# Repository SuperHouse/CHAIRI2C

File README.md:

Chair I2C Interface
===================
Copyright 2020 SuperHouse Automation Pty Ltd <www.superhouse.tv>  
Designed by Jonathan Oxer

Connects to a Permobil electric wheelchair controller, and emulates the
signls from a wheelchair joystick so that the chair can be controlled
electronically. Provides an I2C interface for connection to a host
microcontroller.

Also exposes the "5th Button" and 12V 100mA chair power connections.

Features:

 * 1 x chair controller output.
 * I2C interface.
 * Derives 12V power from the host wheelchair controller.
 * Requires 2.7-5.5V external logic power.

More information is available at:

  http://www.superhouse.tv/chairi2c

INSTALLATION
------------
The design is saved as an EAGLE project. EAGLE PCB design software is
available from www.cadsoftusa.com free for non-commercial use. To use
this project download it and place the directory containing these files
into the "eagle" directory on your computer. Then open EAGLE and
navigate to the project.

DISTRIBUTION
------------
The specific terms of distribution of this project are governed by the
license referenced below.

LICENSE
-------
Licensed under the TAPR Open Hardware License (www.tapr.org/OHL).
The "license" folder within this repository also contains a copy of
this license in plain text format.

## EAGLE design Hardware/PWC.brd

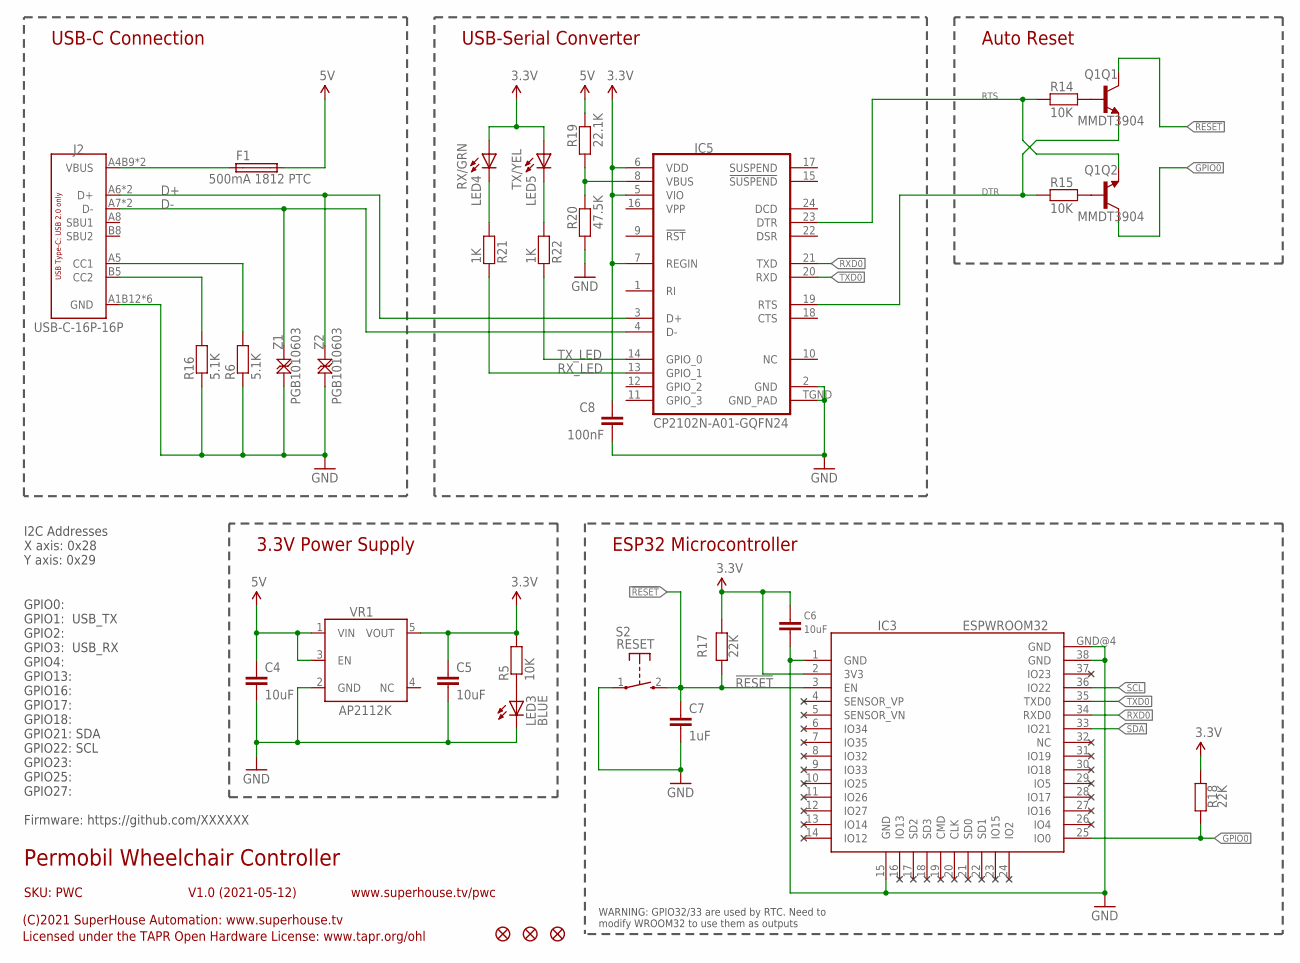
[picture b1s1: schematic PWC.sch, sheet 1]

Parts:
C4, C5, C6: 10uF; C0805
C7: 1uF; C0603
C8: 100nF; C0603
F1: 500mA 1812 PTC; 1812
IC3: ESPWROOM32
IC5: CP2102N-A01-GQFN24; QFN-24
J2: USB-C-16P-16P; USB-C-16P
LED3: BLUE; LED-0603
LED4: RX/GRN; LED-0603
LED5: TX/YEL; LED-0603
Q1: MMDT3904; SOT-363
R5, R14, R15: 10K; R0603
R6, R16: 5.1K; R0603
R17, R18: 22K; R0603
R19: 22.1K; R0603
R20: 47.5K; R0603
R21, R22: 1K; R0603
S2: RESET; TACTILE_SMT_3X4X2
U$35, U$36, U$37: FIDUCIAL1X2; FIDUCIAL-1X2
VR1: AP2112KSOT25; SOT23-5
Z1, Z2: PGB1010603; TVS0603

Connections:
3.3V: C5.1, C6.1, C8.1, IC3.2 (3V3), IC5.5 (VIO), IC5.6 (VDD), IC5.7 (REGIN), LED4.A, LED5.A, R5.2, R17.1, R18.1, VR1.5 (VOUT); also elsewhere on the board
5V: C4.1, F1.2, R19.2, VR1.1 (VIN), VR1.3 (EN)
!RESET: C7.1, IC3.3 (EN), Q1.3 (C), R17.2, S2.2 (S)
D+: IC5.3 (D+), J2.A6 (D+), J2.B6 (D+), Z2.2
D-: IC5.4 (D-), J2.A7 (D-), J2.B7 (D-), Z1.2
DTR: IC5.23 (DTR), Q1.1 (E), R14.1
GND: C4.2, C5.2, C6.2, C7.2, C8.2, IC3.1 (GND), IC3.15 (GND), IC3.38 (GND), IC3.GND@4 (GND), IC5.2 (GND), IC5.TGND (GND_PAD), J2.A1B12 (GND), J2.A12B1 (GND), J2.FIX1 (GND), J2.FIX2 (GND), J2.FIX3 (GND), J2.FIX4 (GND), LED3.C, R6.1, R16.1, R20.1, S2.1, VR1.2 (GND), Z1.1, Z2.1; also elsewhere on the board
GPIO0: IC3.25 (IO0), Q1.6 (C), R18.2
unnamed: LED3.A, R5.1
unnamed: Q1.5 (B), R14.2
unnamed: Q1.2 (B), R15.2
unnamed: LED4.C, R21.2
unnamed: J2.B5 (CC2), R16.2
unnamed: J2.A5 (CC1), R6.2
unnamed: LED5.C, R22.2
unnamed: IC5.8 (VBUS), R19.1, R20.2
RTS: IC5.19 (RTS), Q1.4 (E), R15.1
RXD0: IC3.34 (RXD0), IC5.21 (TXD)
RX_LED: IC5.13 (GPIO_1), R21.1
SCL: IC3.36 (IO22); also elsewhere on the board
SDA: IC3.33 (IO21); also elsewhere on the board
TXD0: IC3.35 (TXD0), IC5.20 (RXD)
TX_LED: IC5.14 (GPIO_0), R22.1
VIN: F1.1, J2.A4B9 (VBUS), J2.A9B4 (VBUS)

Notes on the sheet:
USB-C Connection
USB-Serial Converter
Auto Reset
3.3V Power Supply
ESP32 Microcontroller
WARNING: GPIO32/33 are used by RTC. Need to modify WROOM32 to use them as outputs
GPIO0: GPIO1: USB_TX GPIO2: GPIO3: USB_RX GPIO4: GPIO13: GPIO16: GPIO17: GPIO18: GPIO21: SDA GPIO22: SCL GPIO23: GPIO25: GPIO27: Firmware: https://github.com/XXXXXX
Permobil Wheelchair Controller
V1.0 (2021-05-12)
SKU: PWC
(C)2021 SuperHouse Automation: www.superhouse.tv
Licensed under the TAPR Open Hardware License: www.tapr.org/ohl
www.superhouse.tv/pwc
I2C Addresses X axis: 0x28 Y axis: 0x29

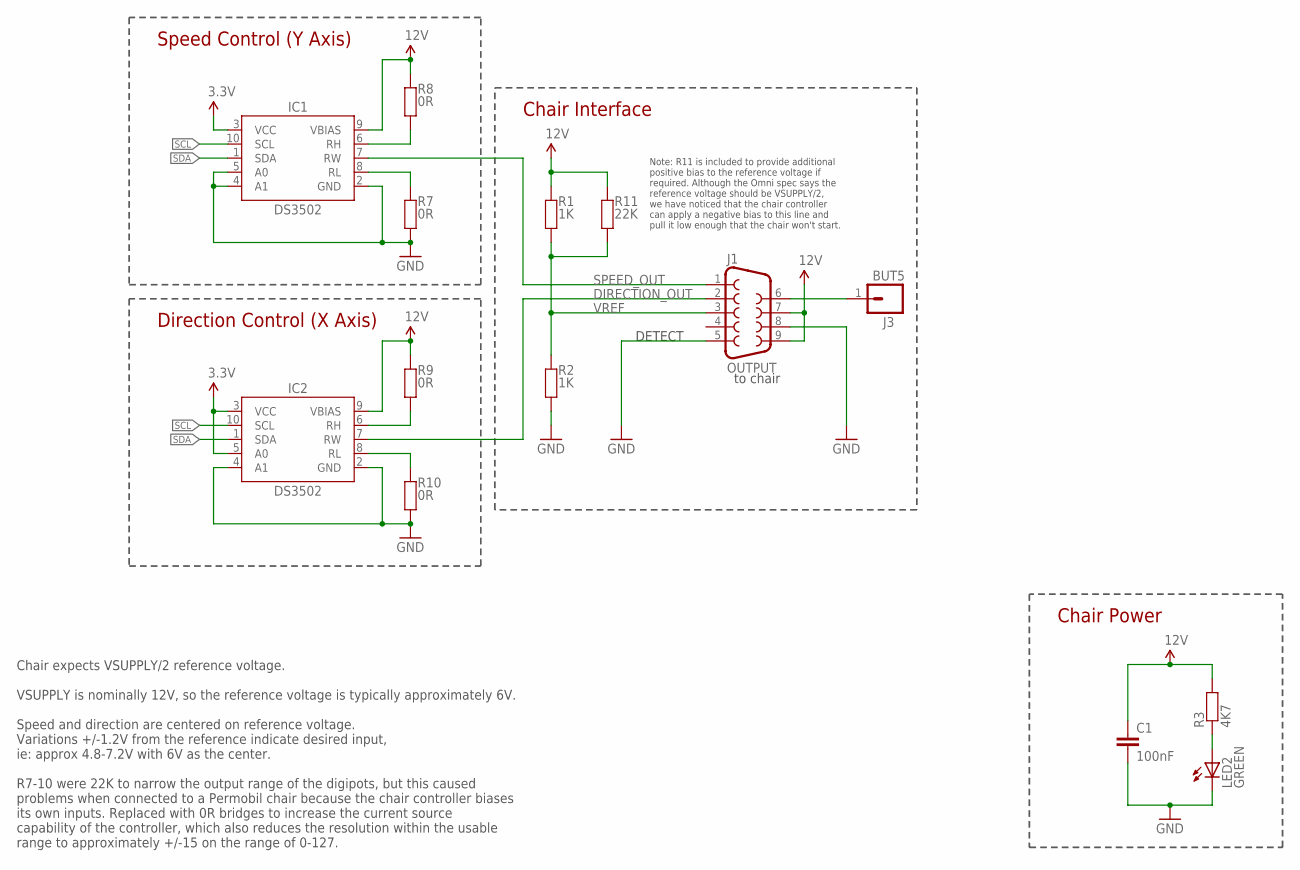
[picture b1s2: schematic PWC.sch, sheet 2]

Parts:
C1: 100nF; C0603
IC1, IC2: DS3502; MSOP10
J1: OUTPUT; DB9-PCB-SOCKET
J3: BUT5; 1X01
LED2: GREEN; LED-0603
R1, R2: 1K; R0603
R3: 4K7; R0603
R7, R8, R9, R10: 0R; R0603
R11: 22K; R0603

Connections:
3.3V: IC1.3 (VCC), IC2.3 (VCC), IC2.5 (A0); also elsewhere on the board
12V: C1.1, IC1.9 (VBIAS), IC2.9 (VBIAS), J1.7, J1.9, R1.2, R3.2, R8.2, R9.2, R11.2
BUT5: J1.6, J3.1
DIRECTION_OUT: IC2.7 (RW), J1.2
GND: C1.2, IC1.2 (GND), IC1.4 (A1), IC1.5 (A0), IC2.2 (GND), IC2.4 (A1), J1.5, J1.8, LED2.C, R2.1, R7.1, R10.1; also elsewhere on the board
unnamed: IC1.6 (RH), R8.1
unnamed: IC2.6 (RH), R9.1
unnamed: IC1.8 (RL), R7.2
unnamed: LED2.A, R3.1
unnamed: IC2.8 (RL), R10.2
SCL: IC1.10 (SCL), IC2.10 (SCL); also elsewhere on the board
SDA: IC1.1 (SDA), IC2.1 (SDA); also elsewhere on the board
SPEED_OUT: IC1.7 (RW), J1.1
VREF: J1.3, R1.1, R2.2, R11.1

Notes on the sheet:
to chair
Direction Control (X Axis)
Speed Control (Y Axis)
Chair Interface
Note: R11 is included to provide additional positive bias to the reference voltage if required. Although the Omni spec says the reference voltage should be VSUPPLY/2, we have noticed that the chair controller can apply a negative bias to this line and pull it low enough that the chair won't start.
DETECT
Chair Power
Chair expects VSUPPLY/2 reference voltage. VSUPPLY is nominally 12V, so the reference voltage is typically approximately 6V. Speed and direction are centered on reference voltage. Variations +/-1.2V from the reference indicate desired input, ie: approx 4.8-7.2V with 6V as the center. R7-10 were 22K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

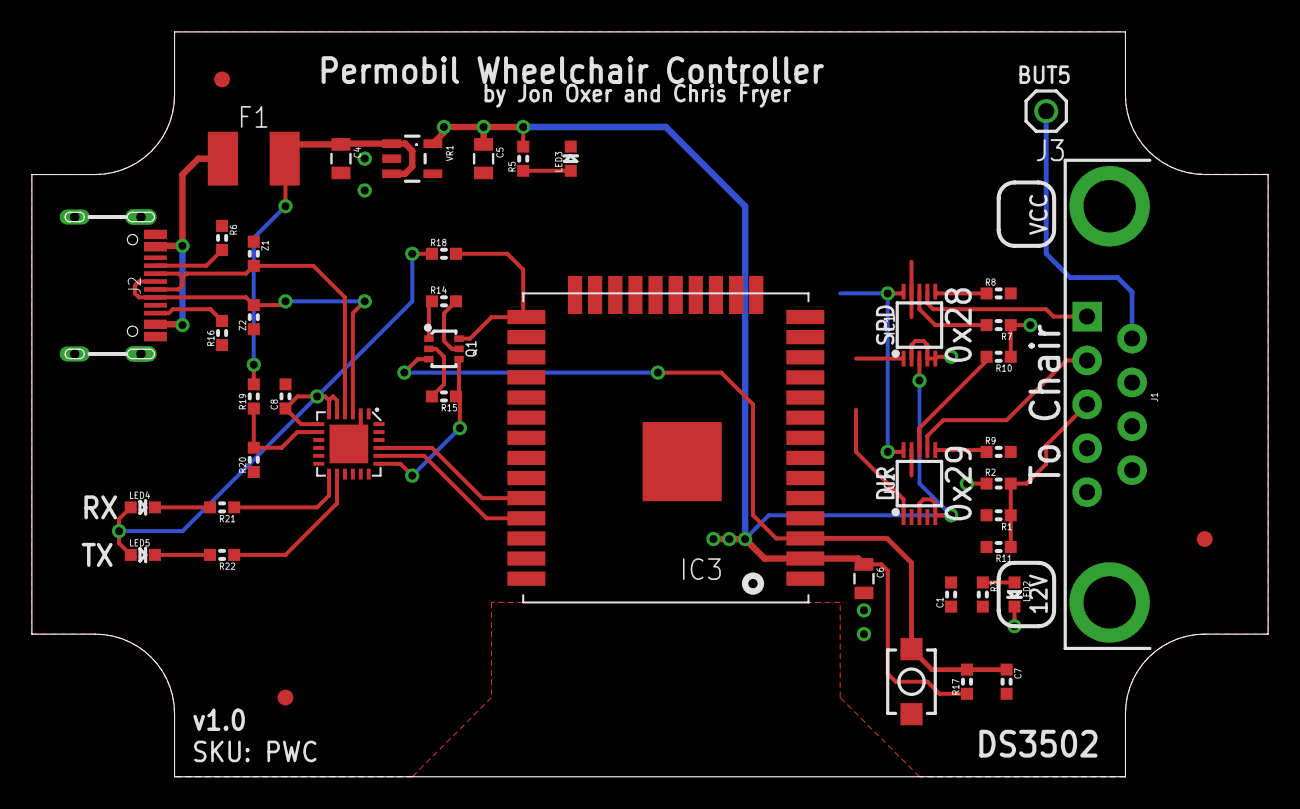
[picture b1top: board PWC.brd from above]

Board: 2 copper layers, 78.0 x 47.0 mm, 45 parts (0 on the bottom side), 34 nets.

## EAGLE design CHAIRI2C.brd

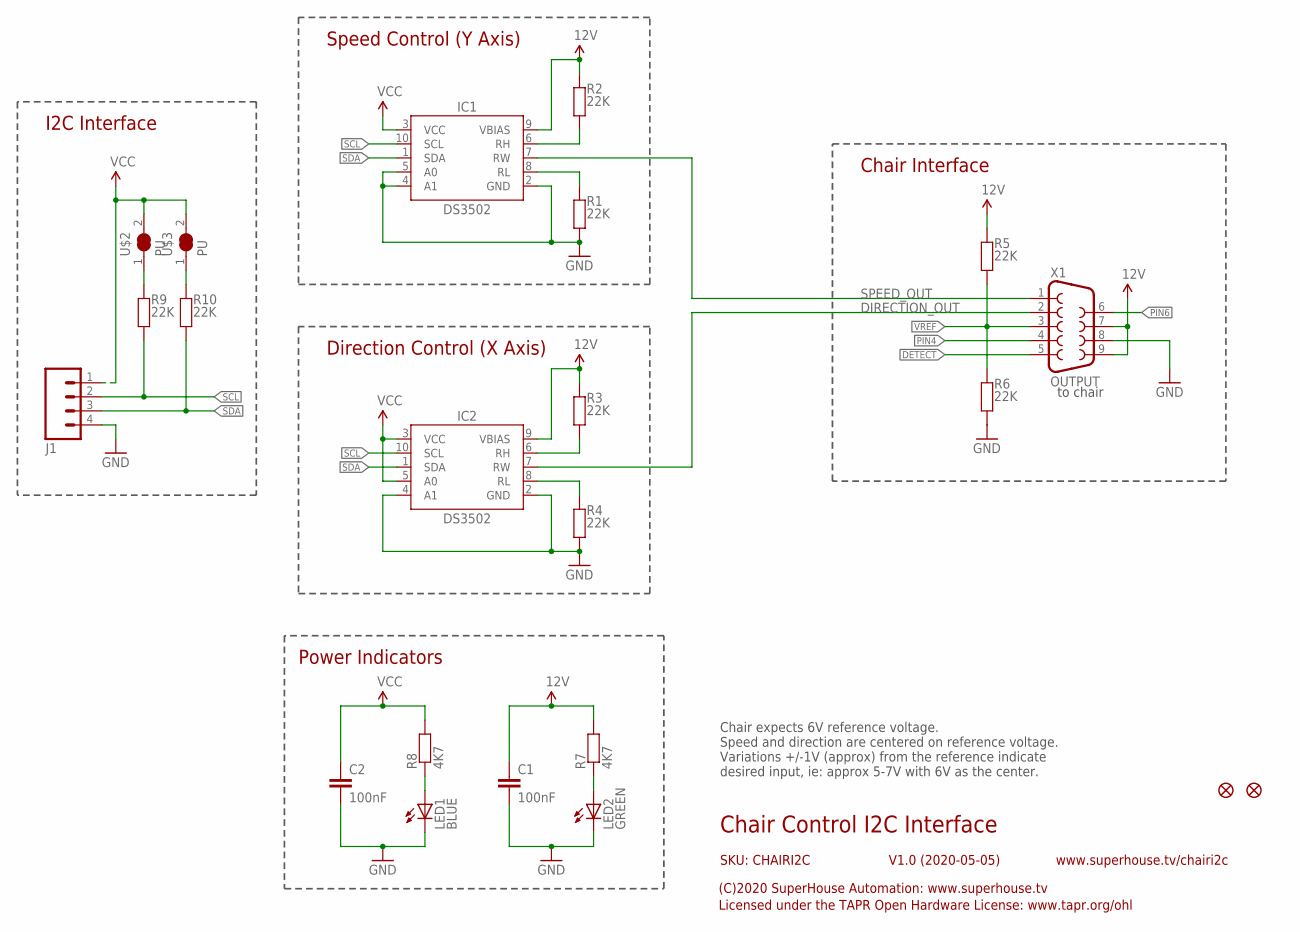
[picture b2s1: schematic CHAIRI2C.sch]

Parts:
C1, C2: 100nF; C0603
IC1, IC2: DS3502; MSOP10
J1: M04-PLAIN; 1X04
LED1: BLUE; LED-0603
LED2: GREEN; LED-0603
R1, R2, R3, R4, R5, R6, R9, R10: 22K; R0603
R7, R8: 4K7; R0603
U$2, U$3: PU; SJC
U$8, U$9: FIDUCIAL1X2.5; FIDUCIAL-1X2.5
X1: OUTPUT; DB9-PCB-SOCKET

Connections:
12V: C1.1, IC1.9 (VBIAS), IC2.9 (VBIAS), R2.2, R3.2, R5.2, R7.2, X1.7, X1.9
DETECT: X1.5
DIRECTION_OUT: IC2.7 (RW), X1.2
GND: C1.2, C2.2, IC1.2 (GND), IC1.4 (A1), IC1.5 (A0), IC2.2 (GND), IC2.4 (A1), J1.4, LED1.C, LED2.C, R1.1, R4.1, R6.1, X1.8
unnamed: R9.2, U$2.1
unnamed: IC1.6 (RH), R2.1
unnamed: IC2.6 (RH), R3.1
unnamed: IC1.8 (RL), R1.2
unnamed: LED1.A, R8.1
unnamed: LED2.A, R7.1
unnamed: R10.2, U$3.1
unnamed: IC2.8 (RL), R4.2
PIN4: X1.4
PIN6: X1.6
SCL: IC1.10 (SCL), IC2.10 (SCL), J1.2, R9.1
SDA: IC1.1 (SDA), IC2.1 (SDA), J1.3, R10.1
SPEED_OUT: IC1.7 (RW), X1.1
VCC: C2.1, IC1.3 (VCC), IC2.3 (VCC), IC2.5 (A0), J1.1, R8.2, U$2.2, U$3.2
VREF: R5.1, R6.2, X1.3

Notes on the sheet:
to chair
Chair Control I2C Interface
V1.0 (2020-05-05)
SKU: CHAIRI2C
(C)2020 SuperHouse Automation: www.superhouse.tv
Licensed under the TAPR Open Hardware License: www.tapr.org/ohl
www.superhouse.tv/chairi2c
Power Indicators
Direction Control (X Axis)
Speed Control (Y Axis)
Chair Interface
I2C Interface
Chair expects 6V reference voltage. Speed and direction are centered on reference voltage. Variations +/-1V (approx) from the reference indicate desired input, ie: approx 5-7V with 6V as the center.

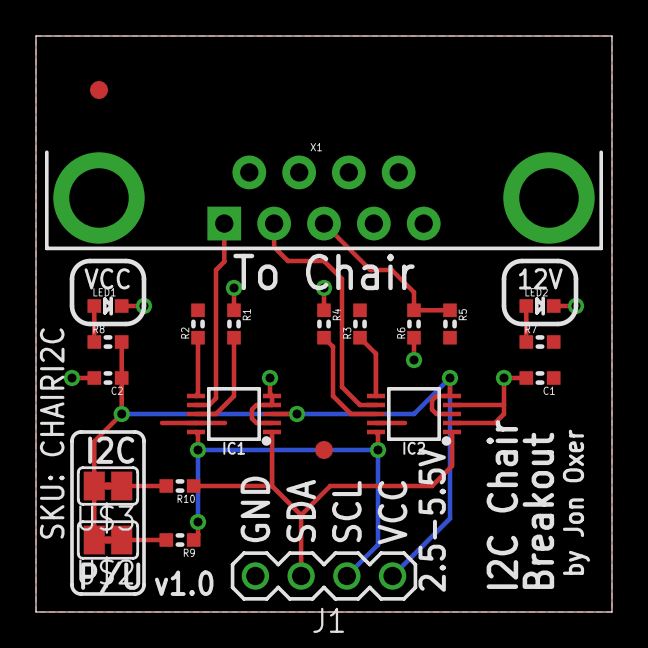
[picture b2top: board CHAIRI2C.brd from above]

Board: 2 copper layers, 32.0 x 32.0 mm, 22 parts (0 on the bottom side), 16 nets.

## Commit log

2020-06-05 Import of first rough draft
2020-06-09 Changed VREF on digital pots for v1.0 release
2020-06-18 Changed reference bias and exposed extra connections
2021-04-13 Moved existing project files into directories.
2021-04-13 Fixed path to image.
2021-04-14 Changed I2C pullups from 10K to 4K7. Moved designators to improve readability.
2021-04-14 Renumbered parts to simplify production setup.
2021-04-14 Added licences.
2021-04-14 Added .gitignore.
2021-04-14 Added images of prototype.
2021-04-14 Replaced render with photo in README.
2021-04-20 Changed output range resistors from 22K to 0R.
2021-04-20 Added test firmware for manually setting digipot output positions.
2021-04-20 Added Photoshop versions of images.
2021-05-11 Forked board files to make version with carrier for XIAO.
2021-05-12 Major conversion to use ESP32 in UB5 plastic box.
2021-05-12 Renamed project files for Permobil version.
2021-05-13 Routing, silkscreen, designators, ERC / DRC for v1.0 release.
2021-05-13 Added render of PWC v1.0 board.
